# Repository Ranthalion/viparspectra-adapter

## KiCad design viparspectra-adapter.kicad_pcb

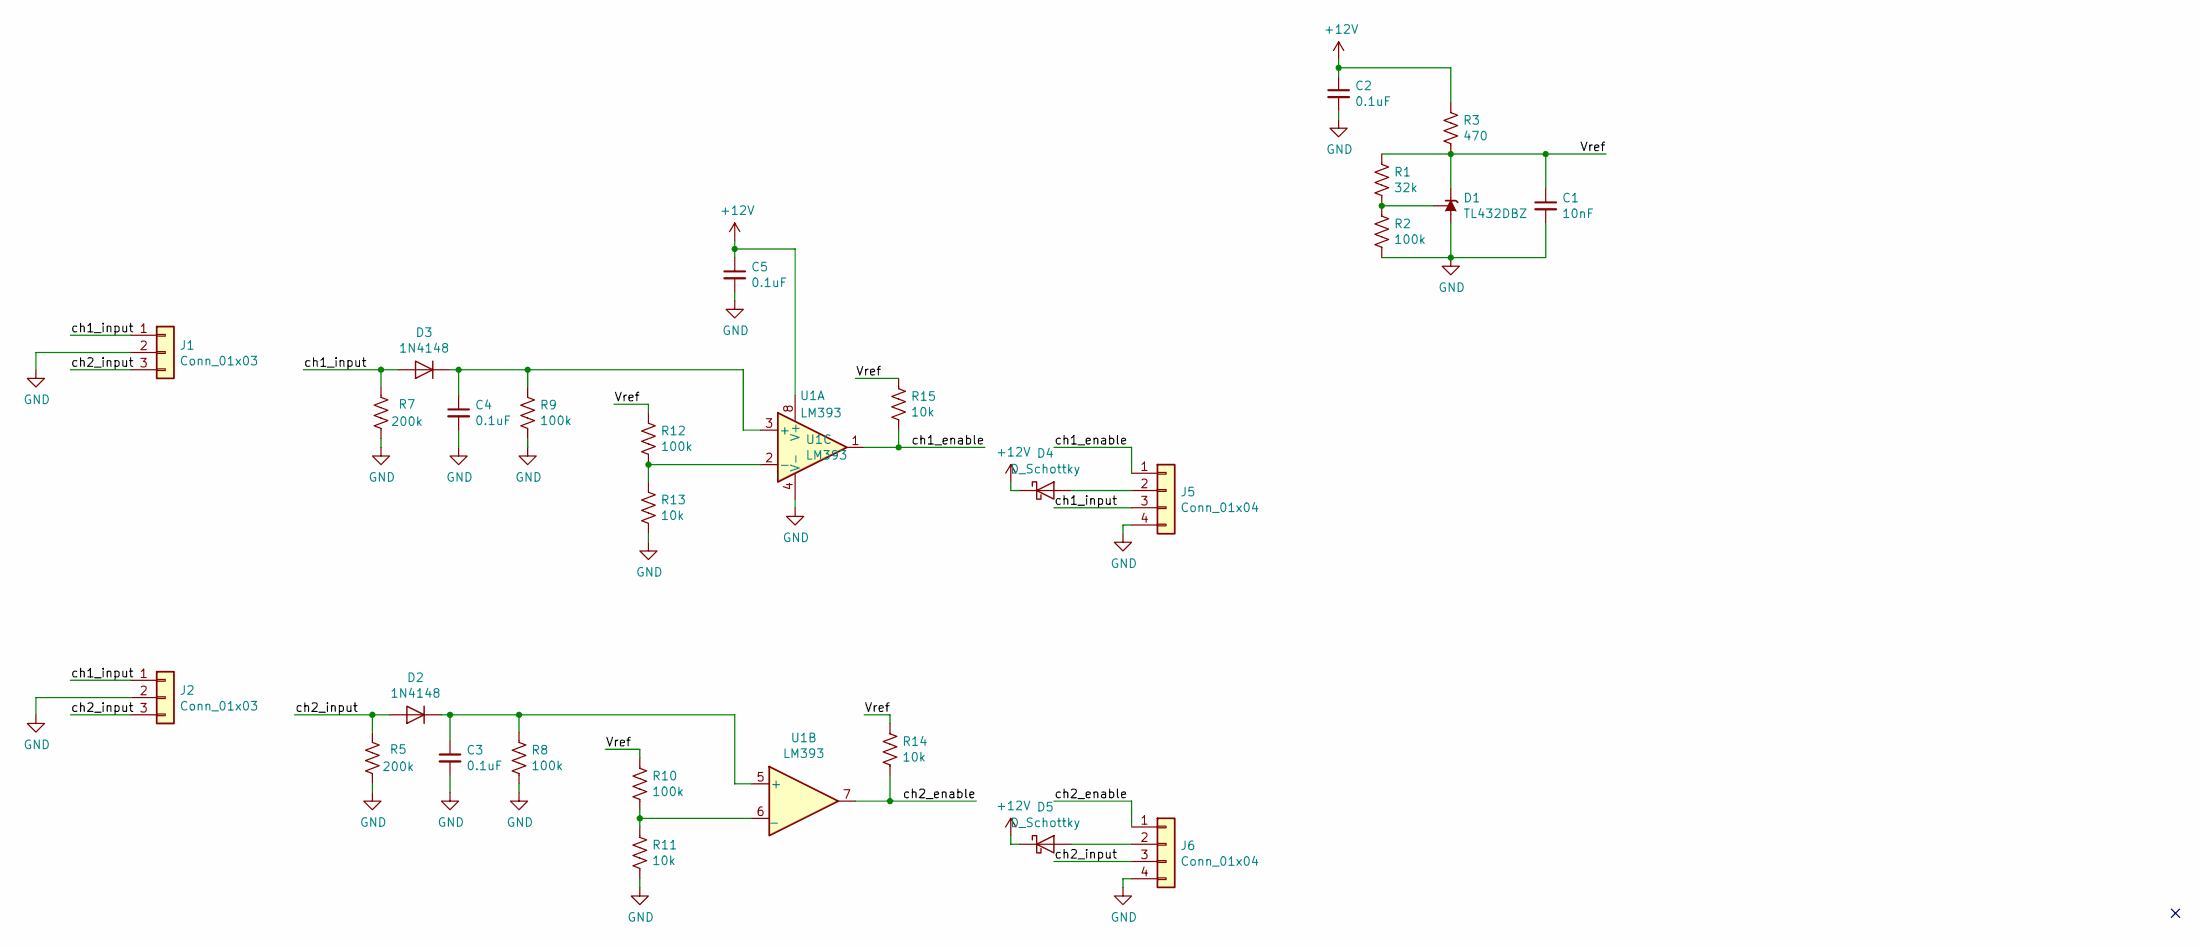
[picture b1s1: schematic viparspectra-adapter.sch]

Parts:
C1: 10nF; C_0603_1608Metric
C2, C3, C4, C5: 0.1uF; C_0603_1608Metric
D1: TL432DBZ; SOT-23
D2, D3: 1N4148; D_0805_2012Metric_Pad1.15x1.40mm_HandSolder
D4, D5: D_Schottky; D_0805_2012Metric_Pad1.15x1.40mm_HandSolder
J1, J2: Conn_01x03; JST_XH_B03B-XH-A_1x03_P2.50mm_Vertical
J5, J6: Conn_01x04; JST_XH_B04B-XH-A_1x04_P2.50mm_Vertical
R1: 32k; R_0603_1608Metric_Pad1.05x0.95mm_HandSolder
R2, R8, R9, R10, R12: 100k; R_0603_1608Metric_Pad1.05x0.95mm_HandSolder
R3: 470; R_0603_1608Metric_Pad1.05x0.95mm_HandSolder
R5, R7: 200k; R_0603_1608Metric_Pad1.05x0.95mm_HandSolder
R11, R13, R14, R15: 10k; R_0603_1608Metric_Pad1.05x0.95mm_HandSolder
U1: LM393; SOIC-8_3.9x4.9mm_P1.27mm

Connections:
+12V: C2.1, C5.1, D4.1 (K), D5.1 (K), R3.1, U1.8 (V+)
/Vref: C1.1, D1.2 (K), R1.1, R3.2, R10.1, R12.1, R14.1, R15.1
/ch1_enable: J5.1, R15.2, U1.1
/ch1_input: D3.2 (A), J1.1, J2.1, J5.3, R7.2
/ch2_enable: J6.1, R14.2, U1.7
/ch2_input: D2.2 (A), J1.3, J2.3, J6.3, R5.2
GND: C1.2, C2.2, C3.2, C4.2, C5.2, D1.3 (A), J1.2, J2.2, J5.4, J6.4, R2.2, R5.1, R7.1, R8.2, R9.2, R11.2, R13.2, U1.4 (V-)
unnamed: C3.1, D2.1 (K), R8.1, U1.5 (+)
unnamed: C4.1, D3.1 (K), R9.1, U1.3 (+)
unnamed: D1.1 (REF), R1.2, R2.1
unnamed: D4.2 (A), J5.2
unnamed: D5.2 (A), J6.2
unnamed: R10.2, R11.1, U1.6 (_)
unnamed: R12.2, R13.1, U1.2 (-)

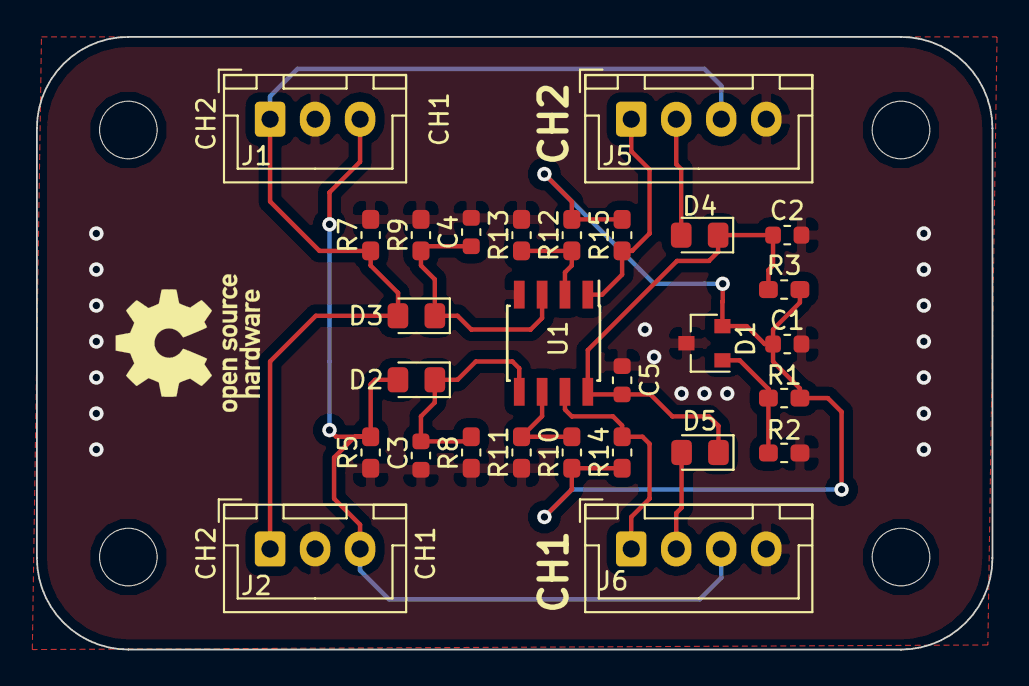
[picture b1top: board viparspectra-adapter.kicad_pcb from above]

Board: 2 copper layers, 53.1 x 34.0 mm, 28 parts (0 on the bottom side), 14 nets.

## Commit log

2020-05-07 schematics and layout
